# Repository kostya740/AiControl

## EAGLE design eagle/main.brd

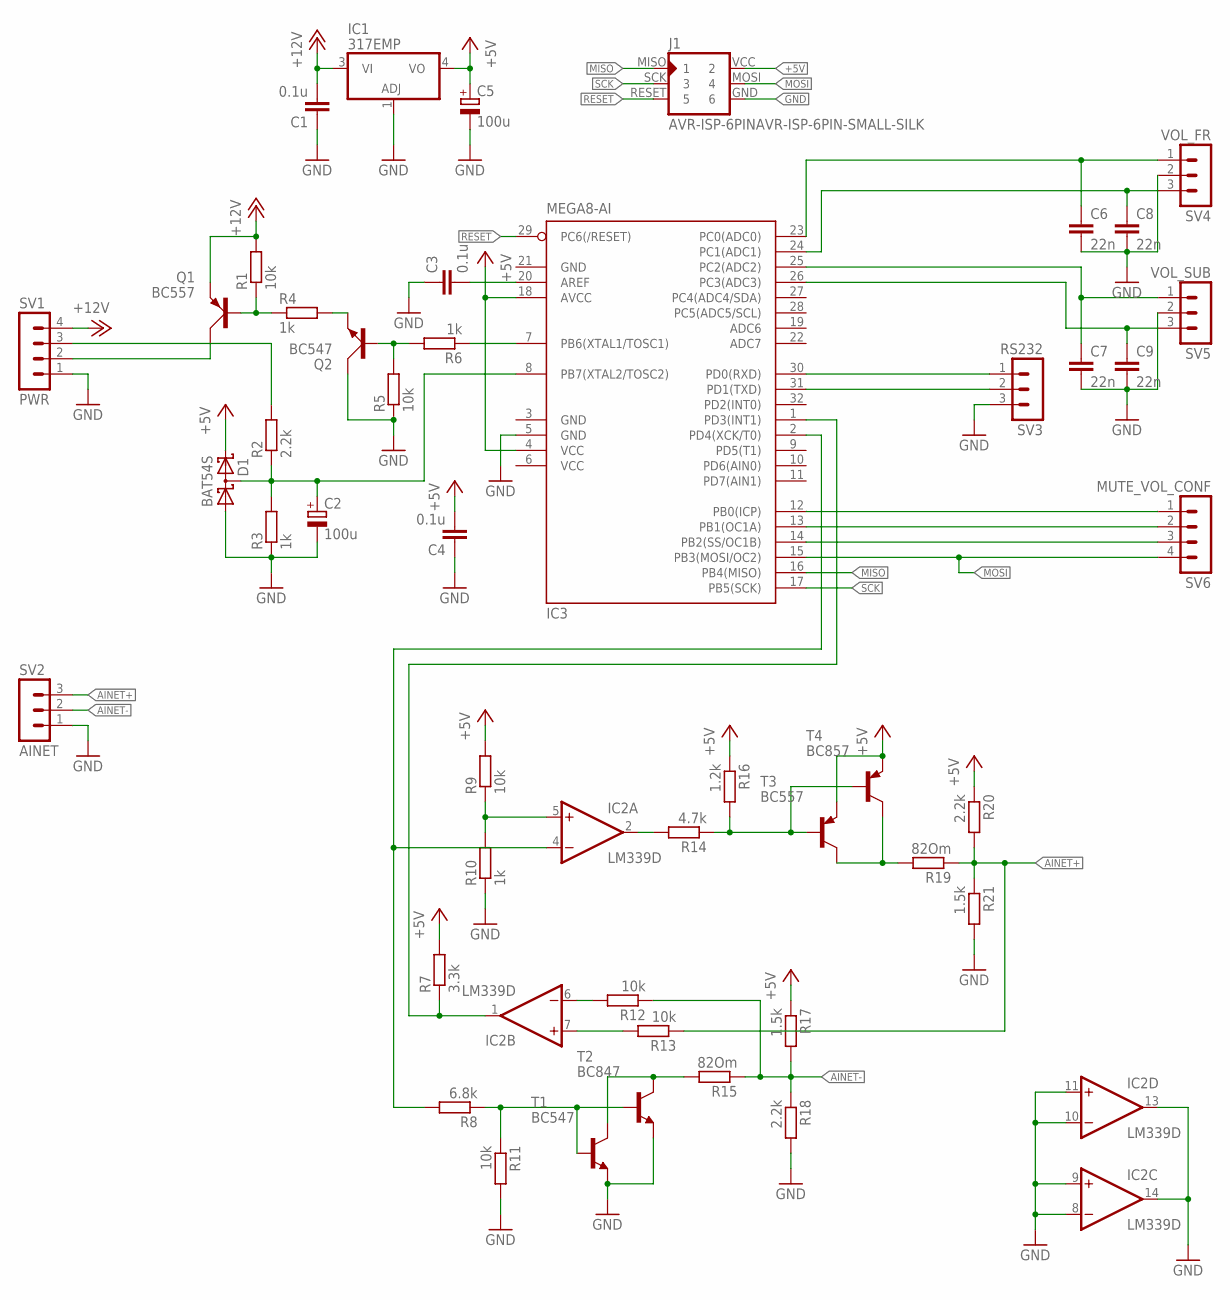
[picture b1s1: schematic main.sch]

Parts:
C1, C3, C4: 0.1u; C0805
C2, C5: 100u; E3,5-8
C6, C7, C8, C9: 22n; C0805
D1: BAT54S; SOT23
IC1: 317EMP; SOT223
IC2: LM339D; SO14
IC3: MEGA8-AI; TQFP32-08
J1: AVR-ISP-6PINAVR-ISP-6PIN-SMALL-SILK; AVR-ISP-6PIN-SMAILL-SILK
Q1: BC557; SOT54A
Q2: BC547; SOT54A
R1, R5, R9, R11, R12, R13: 10k; R0805
R2, R18, R20: 2.2k; R0805
R3, R4, R6, R10: 1k; R0805
R7: 3.3k; R0805
R8: 6.8k; R0805
R14: 4.7k; R0805
R15, R19: 82Om; R0805
R16: 1.2k; R0805
R17, R21: 1.5k; R0805
SV1: PWR; MA04-1
SV2: AINET; MA03-1
SV3: RS232; MA03-1
SV4: VOL_FR; MA03-1
SV5: VOL_SUB; MA03-1
SV6: MUTE_VOL_CONF; MA04-1
T1: BC547; TO92-CBE
T2: BC847; SOT23-BEC
T3: BC557; TO92-EBC
T4: BC857; SOT23-BEC

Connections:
+5V: C4.2, C5.+, D1.2 (C2), IC1.4 (VO), IC3.4 (VCC), IC3.18 (AVCC), J1.VCC (2), R7.2, R9.2, R16.1, R17.1, R20.1, T3.E, T4.E
+12V: C1.2, IC1.3 (VI), Q1.E, R1.2, SV1.4
AINET+: R13.1, R19.1, R20.2, R21.1, SV2.3
AINET-: R12.1, R15.1, R17.2, R18.1, SV2.2
GND: C1.1, C2.-, C3.1, C4.1, C5.-, C6.2, C7.2, C8.2, C9.2, D1.1 (A1), IC1.1 (ADJ), IC2.8 (-IN), IC2.9 (+IN), IC2.10 (-IN), IC2.11 (+IN), IC2.12 (GND), IC2.13 (OUT), IC2.14 (OUT), IC3.3 (GND), IC3.5 (GND), IC3.21 (GND), J1.GND (6), Q2.C, R3.1, R5.1, R10.1, R11.2, R18.2, R21.2, SV1.1, SV2.1, SV3.3, SV4.2, SV5.2, T1.E, T2.E
MISO: IC3.16 (PB4(MISO)), J1.MISO (1)
MOSI: IC3.15 (PB3(MOSI/OC2)), J1.MOSI (4), SV6.4
unnamed: C8.1, IC3.24 (PC1(ADC1)), SV4.3
unnamed: C6.1, IC3.23 (PC0(ADC0)), SV4.1
unnamed: C2.+, D1.3 (C1A2), IC3.8 (PB7(XTAL2/TOSC2)), R2.1, R3.2
unnamed: IC3.12 (PB0(ICP)), SV6.1
unnamed: C9.1, IC3.26 (PC3(ADC3)), SV5.3
unnamed: C7.1, IC3.25 (PC2(ADC2)), SV5.1
unnamed: IC3.13 (PB1(OC1A)), SV6.2
unnamed: IC3.14 (PB2(SS/OC1B)), SV6.3
unnamed: Q2.B, R5.2, R6.2
unnamed: R2.2, SV1.3
unnamed: IC3.7 (PB6(XTAL1/TOSC1)), R6.1
unnamed: Q2.E, R4.2
unnamed: Q1.B, R1.1, R4.1
unnamed: Q1.C, SV1.2
unnamed: IC3.30 (PD0(RXD)), SV3.1
unnamed: C3.2, IC3.20 (AREF)
unnamed: IC2.5 (+IN), R9.1, R10.2
unnamed: IC2.1 (OUT), IC3.1 (PD3(INT1)), R7.1
unnamed: IC2.4 (-IN), IC3.2 (PD4(XCK/T0)), R8.2
unnamed: R14.1, R16.2, T3.B, T4.B
unnamed: IC2.2 (OUT), R14.2
unnamed: IC2.6 (-IN), R12.2
unnamed: R19.2, T3.C, T4.C
unnamed: IC2.7 (+IN), R13.2
unnamed: IC3.31 (PD1(TXD)), SV3.2
unnamed: R15.2, T1.C, T2.C
unnamed: R8.1, R11.1, T1.B, T2.B
RESET: IC3.29 (PC6(/RESET)), J1.RESET (5)
SCK: IC3.17 (PB5(SCK)), J1.SCK (3)
V+: IC2.3 (V+)
VCC: IC3.6 (VCC)

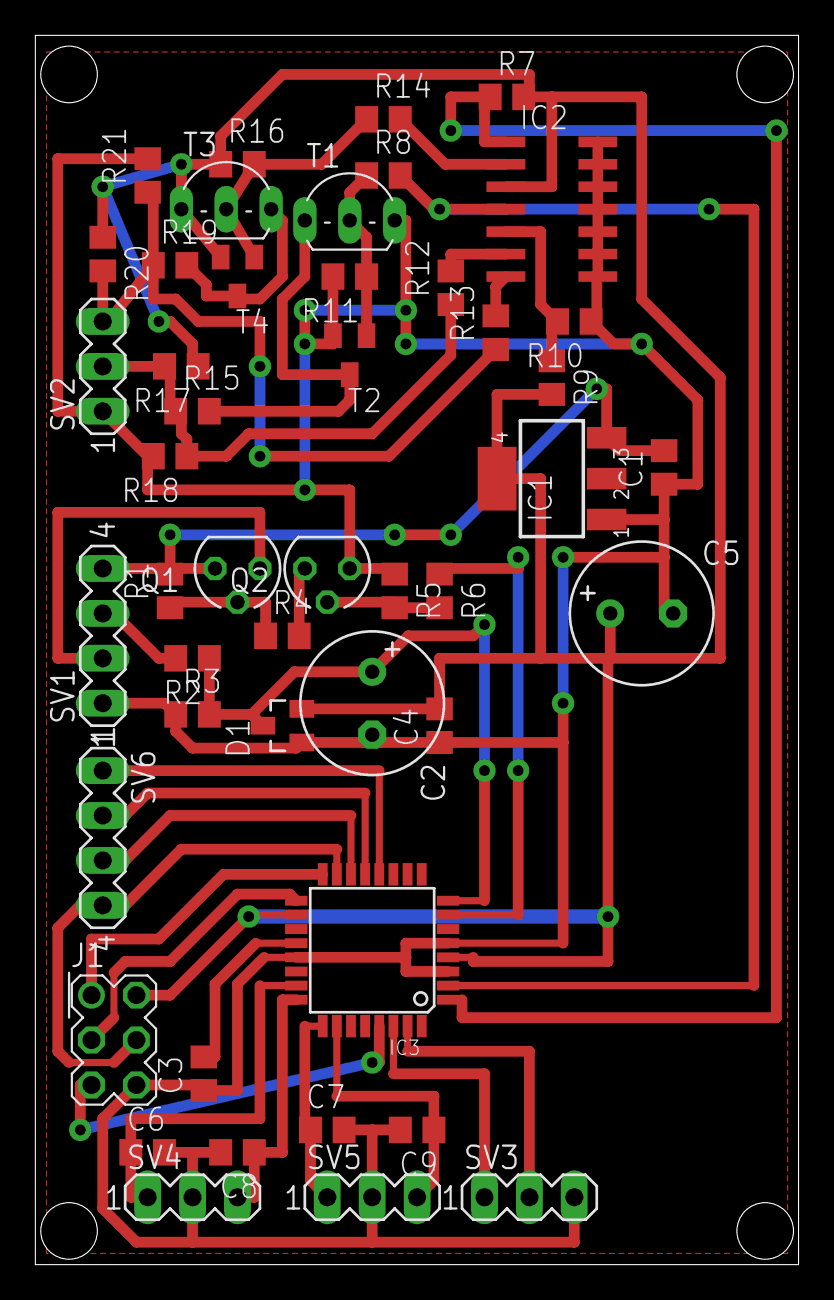
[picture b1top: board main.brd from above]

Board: 2 copper layers, 43.2 x 69.5 mm, 47 parts (0 on the bottom side), 36 nets.
